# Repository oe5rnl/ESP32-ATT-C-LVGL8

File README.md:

# Attenuator Controller

Das Projekt realisiert einen Controller für RF-Attenuators (HF-Dämpfungsglieder).

Es besteht aus einer Basisplatine und den optionalen Bendienelementen:  
* Ein ESP32 CYD Touch-Display  
* Ein 2.8" OLED Display  
* Einen Drehgeber mit Druckschalter  

Der Betrieb kann in folgenden Varianten erfolgen. Basisplatine **und**:  
* Nur ESP Touch Display
* OLED Display und Drehgeber
* ESP Touch Display und oder/und OLED sowie oder/und Drehgeber 

### Firmware installieren (ohne Installation)

Für Endnutzer gibt es im Ordner [install/](install/) einen Offline-Flasher, der
ohne PlatformIO oder Python auskommt — es wird nur ein mitgeliefertes Programm
aufgerufen. Details siehe [install/README.md](install/README.md).

- **ESP32:** Board per USB anstecken und `flash-esp32.sh` (Linux) bzw.
  `flash-esp32.bat` (Windows) ausführen. Der serielle Port wird automatisch
  erkannt; das eigenständige `esptool` ist bereits enthalten.
- **Pico:** **BOOTSEL** gedrückt halten, einstecken und `firmware/firmware.uf2`
  auf das Laufwerk `RPI-RP2` kopieren — ganz ohne Zusatzprogramm.

> **Hinweis:** Die auslieferbaren Firmware-Dateien werden vom Entwickler einmalig
> per [install/export.sh](install/export.sh) erzeugt (baut ESP32 + Pico und legt
> `firmware-merged.bin` sowie `firmware.uf2` in `install/firmware/` ab).

---

## Systemübersicht

ESP32 CYD (Touch-Display 320×240, WebGUI via WiFi, LVGL 8 UI) kommuniziert über
UART (115200 Baud) mit dem Raspberry Pi Pico (Drehgeber, SSD1306 OLED). Beide
steuern gemeinsam die Attenuator-Relais.

Der am häufigsten Abzutreffende Attenuatos ist die 135dB Variante.  
Siehe dazu zur Verkabelung ATT_135db.md  
Test der EinzelRelais mit dem Testmenü am Display und auf der Webseite.

### ESP32 — Touch-Controller

LVGL-8-Steuerungsoberfläche auf ESP32 CYD (Cheap Yellow Display):

- 2.8" Touch-Display ILI9341 (320×240), Variante CYD2USB mit ST7789
- WLAN: AP-Modus und Client-Modus gleichzeitig
- WebGUI mit identischer Funktion wie das Touch-Display
- NVS-Persistenz (Wert, Presets, WiFi-Modus, Set-Modus)
- FreeRTOS Dual-Core: LVGL/UI auf Core 1, WebSocket/WiFi auf Core 0
- Kommunikation mit dem Pico über UART0

### Pico — Relais-/Drehgeber-Controller

Raspberry Pi Pico als Attenuator-Controller:

- Drehgeber zur Auswahl und Aktivierung von Dämpfungswerten
- Optionales SSD1306 OLED-Display (I2C)
- Automatische Attenuator-Erkennung über ADC (Spannungsteiler an GP26 / ADC0)
- Bis zu 8 bistabile Relais (H-Brücke oder Einzel-Pin)
- Serielle Steuerung über UART vom ESP32

---

## Unterstützte Attenuatoren

Quelle: [pico/src/Attenuator.cpp](pico/src/Attenuator.cpp),
[pico/src/att_types.h](pico/src/att_types.h) und die jeweiligen `att_*`-Klassen.

| Typ | Max. dB | Schritte | Relay-Modus | Status im Code |
|-----|--------:|---------:|-------------|----------------|
| R&S 26.5 GHz | 110 dB | 10 dB | Static (Einzelpin) | implementiert (`Att26GHz`) |
| R&S RS-135 dB | 135 dB | 5 dB | Bridge (H-Brücke) | implementiert (`Att135dB`) |
| RS-141 dB | (variable Pads) | — | Bridge (H-Brücke) | implementiert (`Att141dB`) |
| Typ B | — | — | — | **nicht** implementiert (`AttB` → „NOT IMPLEMENTED") |

### Automatische Erkennung über ADC (GP26 / ADC0)

**Maßgeblich ist der Code** in [pico/src/main.cpp](pico/src/main.cpp) (`getAttenuator()`):

| Spannung (v) | Erkannter Attenuator |
|--------------|----------------------|
| 0.0 V ≤ v < 0.7 V | RS-141 dB |
| 0.9 V ≤ v < 1.5 V | 26.5 GHz |
| 1.7 V ≤ v < 2.3 V | Typ B |
| 2.4 V ≤ v ≤ 3.3 V | RS-135 dB |
| außerhalb aller Fenster | **NOT IMPLEMENTED** — kein Attenuator, kein GPIO wird gesetzt |

> **Hinweis:** Die alten READMEs und der Kommentar in
> [pico/src/att_types.h](pico/src/att_types.h) nennen eine andere Zuordnung
> (0.0–0.8 V → 26.5 GHz usw.). Diese stimmt **nicht** mit dem aktuellen Code
> überein. Ungültige Spannungen (Lücken 0.7–0.9 / 1.5–1.7 / 2.3–2.4 V sowie alles
> außerhalb) liefern `getAttenuator()` = `-1`; `create_attenuator()` gibt dann
> `nullptr` zurück, es wird **kein GPIO** aktiviert und das Display zeigt
> „NOT IMPLEMENTED".

### Widerstände für den Spannungsteiler

R10 nach 3,3 V, R11 nach GND (an Pico ADC):

```
 3,3V
  |
 R10
  |---- Pico ADC (GP26)
  |
 R11
  |
 GND
```

| Attenuator | R10 | R11 |
|------------|-----|-----|
| 26.5 GHz | offen | offen |
| RS-141 dB | 3k3 | 4k7 |
| Typ B | 4k7 | 3k3 |
| RS-135 dB | 0 Ohm | offen |

> **ACHTUNG:** Niemals zwei 0-Ohm-Widerstände einbauen — das kurzschließt den
> 3,3-V-Ausgang des Pico.
>
> **ACHTUNG:** Vor dem Verbinden des Attenuators mit der Steuerplatine am Display
> prüfen, ob der gewünschte Attenuator angezeigt wird. Wird `ATTENUATOR_26_5GHz`
> eingestellt, aber ein Attenuator mit H-Brücken-Ansteuerung verwendet, kann es
> zur Zerstörung der Relais führen.

---

## Hardware

### Pico — GPIO-Belegung

| Pin | GPIO | Funktion |
|-----|------|----------|
| 1  | GP0  | TX → ESP32 (Serial1) |
| 2  | GP1  | RX ← ESP32 (Serial1) |
| 4  | GP2  | Relais 1a |
| 5  | GP3  | Relais 1b |
| 6  | GP4  | I2C SDA (Display) |
| 7  | GP5  | I2C SCL (Display) |
| 9  | GP6  | Relais 2a |
| 10 | GP7  | Relais 2b |
| 11 | GP8  | Relais 3a |
| 12 | GP9  | Relais 3b |
| 14 | GP10 | Relais 4a |
| 15 | GP11 | Relais 4b |
| 16 | GP12 | Relais 5a |
| 17 | GP13 | Relais 5b |
| 19 | GP14 | Relais 6a |
| 20 | GP15 | Relais 6b |
| 21 | GP16 | Relais 7a |
| 22 | GP17 | Relais 7a |
| 24 | GP18 | Relais 8a |
| 25 | GP19 | Encoder SW |
| 26 | GP20 | Encoder DT (B) |   
| 27 | GP21 | Encoder CLK (A) |
| 29 | GP22 | Relais 8b |
| 31 | GP26 | ADC0 — Attenuator-Erkennung |
| 32 | GP27 | Relais 9a |
| 34 | GP28 | Relais 9b |

#### Relais-Mapping RS-135 dB (bistabil, ON/OFF-Pin-Paare)

Quelle: [pico/src/att_135db.h](pico/src/att_135db.h) / [.cpp](pico/src/att_135db.cpp).

| Relais | ON-Pin | OFF-Pin | tatsächlicher Pad-Wert |
|--------|--------|---------|------------------------|
| U1 (40bB A) | GP3 | GP2 | 40 dB |
| U2 (20dB A) | GP7 | GP6 | 20 dB |
| U3 (5 dB) | GP9 | GP8 | 5 dB |
| U4 (20dB B) | GP11 | GP10 | 20 dB |
| U5 (10 dB) | GP13 | GP12 | 10 dB |
| U6 (40dB B) | GP15 | GP14 | 40 dB |
| U7 (RF) | GP17 | GP16 | RF ON/OFF |

#### Relais-Mapping 26.5 GHz (Static, HIGH = aktiv)

Quelle: [pico/src/att_26ghz.h](pico/src/att_26ghz.h).

| Pad | GPIO | Pin |
|-----|------|-----|
| 10 dB | GP10 | 14 |
| 20 dB | GP11 | 15 |
| 40 dB (A) | GP12 | 16 |
| 40 dB (B) | GP13 | 17 |

---

## WiFi-Konfiguration

### WiFi-Credentials einstellen

Erstelle `esp32/src/wifi_credentials.h` mit deinen WLAN-Zugangsdaten (Vorlage:
[esp32/src/wifi_credentials.h.example](esp32/src/wifi_credentials.h.example)):

Der AP ist unabhängig von der Datei stets erreichbar. Die Client-Anbindung ans Heimnetz kann man jederzeit zur Laufzeit über die WebGUII (WLAN-Suche → Verbinden) oder das Display setzen — die Werte landen im NVS. wifi_credentials.h ist nur praktisch, wenn man die Zugangsdaten schon beim Kompilieren fest hinterlegen will (z. B. damit sich das Gerät ohne manuelle Ersteinrichtung direkt verbindet).

```cpp
#pragma once
#define WIFI_SSID     "DeinSSID"
#define WIFI_PASSWORD "DeinPasswort"
```

Diese Datei ist in [.gitignore](.gitignore) und wird nicht committet.

### WiFi-Modi

Quelle: [esp32/src/webserver.h](esp32/src/webserver.h) (`apply_wifi_mode()`).

Es gibt genau **zwei** Modi; jeder von 0 verschiedene Wert wird intern auf `2`
gesetzt. Die Einstellung wird im NVS (`wmode`) gespeichert.

- **Modus 0 (Aus):** WiFi vollständig deaktiviert (`WIFI_OFF`), Webserver und AP
  werden gestoppt, mDNS beendet.
- **Modus 2 (AP + Client):** Der Access Point ist **immer** aktiv. Ein
  Client (STA) wird zusätzlich nur gestartet, wenn gültige Client-Zugangsdaten
  vorliegen — andernfalls läuft das Gerät im AP-only-Betrieb.
  - AP-SSID: `ESP32-ATT`
  - AP-Passwort: `12345678` (Standardwert — bitte ändern)
  - AP-IP: `192.168.4.1`
  - Client-Zugangsdaten stammen aus dem NVS (`wifi_ssid` / `wifi_pass`),
    vorbelegt aus [esp32/src/wifi_credentials.h](esp32/src/wifi_credentials.h);
    zur Laufzeit über das Display-Menü (**Menu → WLAN**) bzw. die WLAN-Suche der
    WebGUI setzbar.
  - Die Client-Verbindung erfolgt nicht blockierend; nach Timeout (ca. 20 s) oder
    bei Fehler fällt das Gerät automatisch auf AP-only zurück.
  - mDNS (`esp32-att.local`) wird erst nach erfolgreicher Client-Verbindung
    aktiviert.

### WebGUI

Nach dem Start erreichbar unter:
- **AP-Modus:** `http://192.168.4.1`
- **Client-Modus:** `http://esp32-att.local` (oder die angezeigte IP)

---

## Quick Start

### ESP32 flashen
```bash
cd esp32
./upload.sh
# oder manuell:
~/.platformio/penv/bin/pio run -t upload
~/.platformio/penv/bin/pio device monitor
# CYD2USB-Variante (ST7789):
~/.platformio/penv/bin/pio run -e cyd2usb -t upload
```

### Pico flashen
```bash
cd pico
./upload_main.sh
# oder manuell:
~/.platformio/penv/bin/pio run -t upload
~/.platformio/penv/bin/pio device monitor
```

> **Tipp:** Falls `pio: command not found` erscheint, den vollen Pfad
> `~/.platformio/penv/bin/pio` verwenden oder PlatformIO global installieren.

**Voraussetzungen:** [PlatformIO](https://platformio.org/) (CLI oder VS-Code-Extension).

### Tools einrichten

1. **Repository holen**
   ```bash
   git clone <REPO-URL>
   cd ESP32-ATT-C-LVGL8
   ```

2. **PlatformIO installieren** — eine der beiden Varianten:
   - **VS Code + Extension (empfohlen):** [VS Code](https://code.visualstudio.com/)
     installieren, dann die Extension **PlatformIO IDE** hinzufügen. Build/Upload
     erfolgen über die PlatformIO-Toolbar.
   - **CLI (Kommandozeile):**
     ```bash
     python3 -m pip install --user platformio
     # oder das offizielle Installskript:
     # curl -fsSL https://raw.githubusercontent.com/platformio/platformio-core-installer/master/get-platformio.py | python3
     ```
     Danach steht `pio` unter `~/.platformio/penv/bin/pio` zur Verfügung
     (ggf. in den `PATH` aufnehmen).

3. **Toolchains & Bibliotheken** — werden beim ersten `pio run` automatisch
   geladen (Platforms `espressif32` und `raspberrypi`, Frameworks und alle
   `lib_deps` aus den jeweiligen [platformio.ini](esp32/platformio.ini)).
   Eine manuelle Installation ist nicht nötig.

4. **Serielle Rechte (Linux):** Für Upload/Monitor den eigenen Benutzer zur
   Gruppe `dialout` hinzufügen und neu anmelden:
   ```bash
   sudo usermod -aG dialout $USER
   ```

5. **WLAN-Zugangsdaten (optional):** Nur nötig, wenn die Client-Zugangsdaten
   bereits beim Kompilieren fest hinterlegt werden sollen — siehe Abschnitt
   „WiFi-Credentials einstellen". Ohne diese Datei ist der Access Point trotzdem
   erreichbar; die Client-Anbindung lässt sich zur Laufzeit über WebGUI/Display
   setzen.

---

## Serielles Kommunikationsprotokoll (UART, 115200 Baud)

Alle Nachrichten sind ASCII-Zeilen, abgeschlossen mit `\n`.

### Pico → ESP32

**Startup-Info** (einmalig nach Pico-Reset):

| Befehl | Beschreibung |
|--------|--------------|
| `RELAYS:<n>` | Anzahl der Relais |
| `ATTNAME:<name>` | Attenuator-Name |
| `STEP:<n>` | Schrittweite in dB |
| `MAXDB:<n>` | Maximalwert in dB |
| `RELMODE:<n>` | Relay-Modus: `0`=Bridge, `1`=Static |
| `RFSWITCH:<n>` | RF-Schalter vorhanden: `0`/`1` |
| `PICOVER:<ver>` | Pico-Firmware-Version |

**Laufzeit:**

| Befehl | Beschreibung |
|--------|--------------|
| `<n>dB` | Aktueller Dämpfungswert (Display-Sync) |
| `SEL<n>` | Ausgewählte Stelle: `0`=Hunderter, `1`=Zehner, `2`=Einer |
| `SETMODE:<n>` | Set-Modus: `0`=Direct, `1`=Time, `2`=Button |
| `RF:<n>` | RF-Schalter-Zustand: `0`/`1` |
| `TESTSTATE:<i>,<s>` | Test: Relais-Index `i`, Zustand `s` (`0`/`1`) |
| `SETOK` | Pico hat im Set-Button-Modus angewendet |

### ESP32 → Pico

| Befehl | Beschreibung |
|--------|--------------|
| `<n>dB` | Dämpfung Display-Sync (kein Schalten) |
| `SET:<n>dB` | Dämpfung sofort schalten (Relais) |
| `TIMED:<n>dB` | Zeitgesteuert schalten |
| `SEL<n>` | Aktive Stelle ändern |
| `SETMODE:<n>` | Set-Modus umschalten |
| `RF:<n>` | RF-Schalter setzen: `0`/`1` |
| `TEST:START` | Relay-Test starten |
| `TEST:SEL:<i>` | Test-Relais `i` auswählen |
| `TEST:ACTION` | Test: Puls/Toggle am gewählten Relais |
| `TEST:END` | Test beenden |

---

## Implementierungsdetails ESP32

| Core | Aufgaben |
|------|----------|
| **Core 0** | WiFi-Stack, AsyncTCP, ESPAsyncWebServer, WebSocket-Callbacks |
| **Core 1** | `setup()` / `loop()`, LVGL `lv_timer_handler()`, UART-Empfang |

Kommunikation zwischen den Cores über FreeRTOS-Queue (`xQueueSend` / `xQueueReceive`).

---

## Projektstruktur

```
ESP32-ATT-C-LVGL8/
├── shared/
│   └── version.h               # Versionsnummern ESP32 + Pico (0.51)
├── esp32/
│   ├── platformio.ini          # PlatformIO + TFT_eSPI Build-Flags
│   ├── lv_conf.h               # LVGL-8-Konfiguration
│   └── src/
│       ├── main.cpp            # LVGL UI, UART-Kommunikation
│       ├── webserver.h         # AsyncWebServer, WebSocket, HTML
│       ├── wifi_credentials.h  # WLAN-Zugangsdaten (nicht im Repo)
│       └── lv_font_digits_72.c # Custom 72 px Ziffern-Font
├── pico/
│   └── src/
│       ├── main.cpp            # Hauptprogramm, UART, Encoder, ADC-Erkennung
│       ├── Attenuator.h/.cpp   # Abstrakte Basisklasse + Factory
│       ├── att_26ghz.h/.cpp    # R&S 26.5 GHz (Static, 110 dB / 10 dB)
│       ├── att_135db.h/.cpp    # R&S 135 dB (Bridge, 135 dB / 5 dB)
│       ├── att_141db.h/.cpp    # RS-141 dB (Bridge)
│       ├── att_b.h/.cpp        # Typ B (nicht implementiert)
│       ├── att_types.h         # Typ-Konstanten + ADC-Grenzwerte (Kommentar veraltet)
│       ├── test.h/.cpp         # Relay-Testmodus
│       ├── SSD1306.h/.cpp      # OLED-Display-Treiber
│       ├── big_digits.h        # Große Ziffern für OLED
│       ├── font.h              # OLED-Font
│       └── toggle_gpio10_13.cpp # Standalone-GPIO-Testhilfe
├── Schaltung/                  # KiCad Schaltplan + PCB
├── install/                    # Offline-Flasher (esptool + Skripte, ohne Installation)
└── docs/                       # Zusätzliche Dokumentation
```

---

## Lizenz

MIT — siehe [LICENSE](LICENSE).

Ausnahme: Der Ordner [esp32/docu/esp32-display/](esp32/docu/esp32-display/)
enthält Hersteller-Dokumentation (Sunton) und ist **nicht** von der MIT-Lizenz
abgedeckt.

Build by OE5RNL & OE5NVL & Chatgpt & Claude

### Haftungsausschluss

Diese Hard- und Software wird „wie besehen" ohne jegliche Gewährleistung
bereitgestellt — weder ausdrücklich noch stillschweigend, insbesondere keine
Gewährleistung der Marktgängigkeit oder Eignung für einen bestimmten Zweck.
Die Nutzung erfolgt auf eigene Gefahr. Die Autoren übernehmen keine Haftung für
Schäden jeglicher Art (z. B. an Attenuatoren, Relais, Messgeräten oder sonstiger
Ausrüstung), die aus dem Aufbau, dem Betrieb oder der Nutzung dieses Projekts
entstehen.

Insbesondere kann eine falsche Attenuator-Erkennung oder fehlerhafte Verdrahtung
zur Zerstörung der Relais oder des angeschlossenen Dämpfungsglieds führen (siehe
Warnhinweise im Abschnitt „Widerstände für den Spannungsteiler"). Vor dem
Anschluss stets prüfen, ob der korrekte Attenuator angezeigt wird.

## Basiert auf

[ESP32-Cheap-Yellow-Display](https://github.com/witnessmenow/ESP32-Cheap-Yellow-Display)
— LVGL8-Beispiel.

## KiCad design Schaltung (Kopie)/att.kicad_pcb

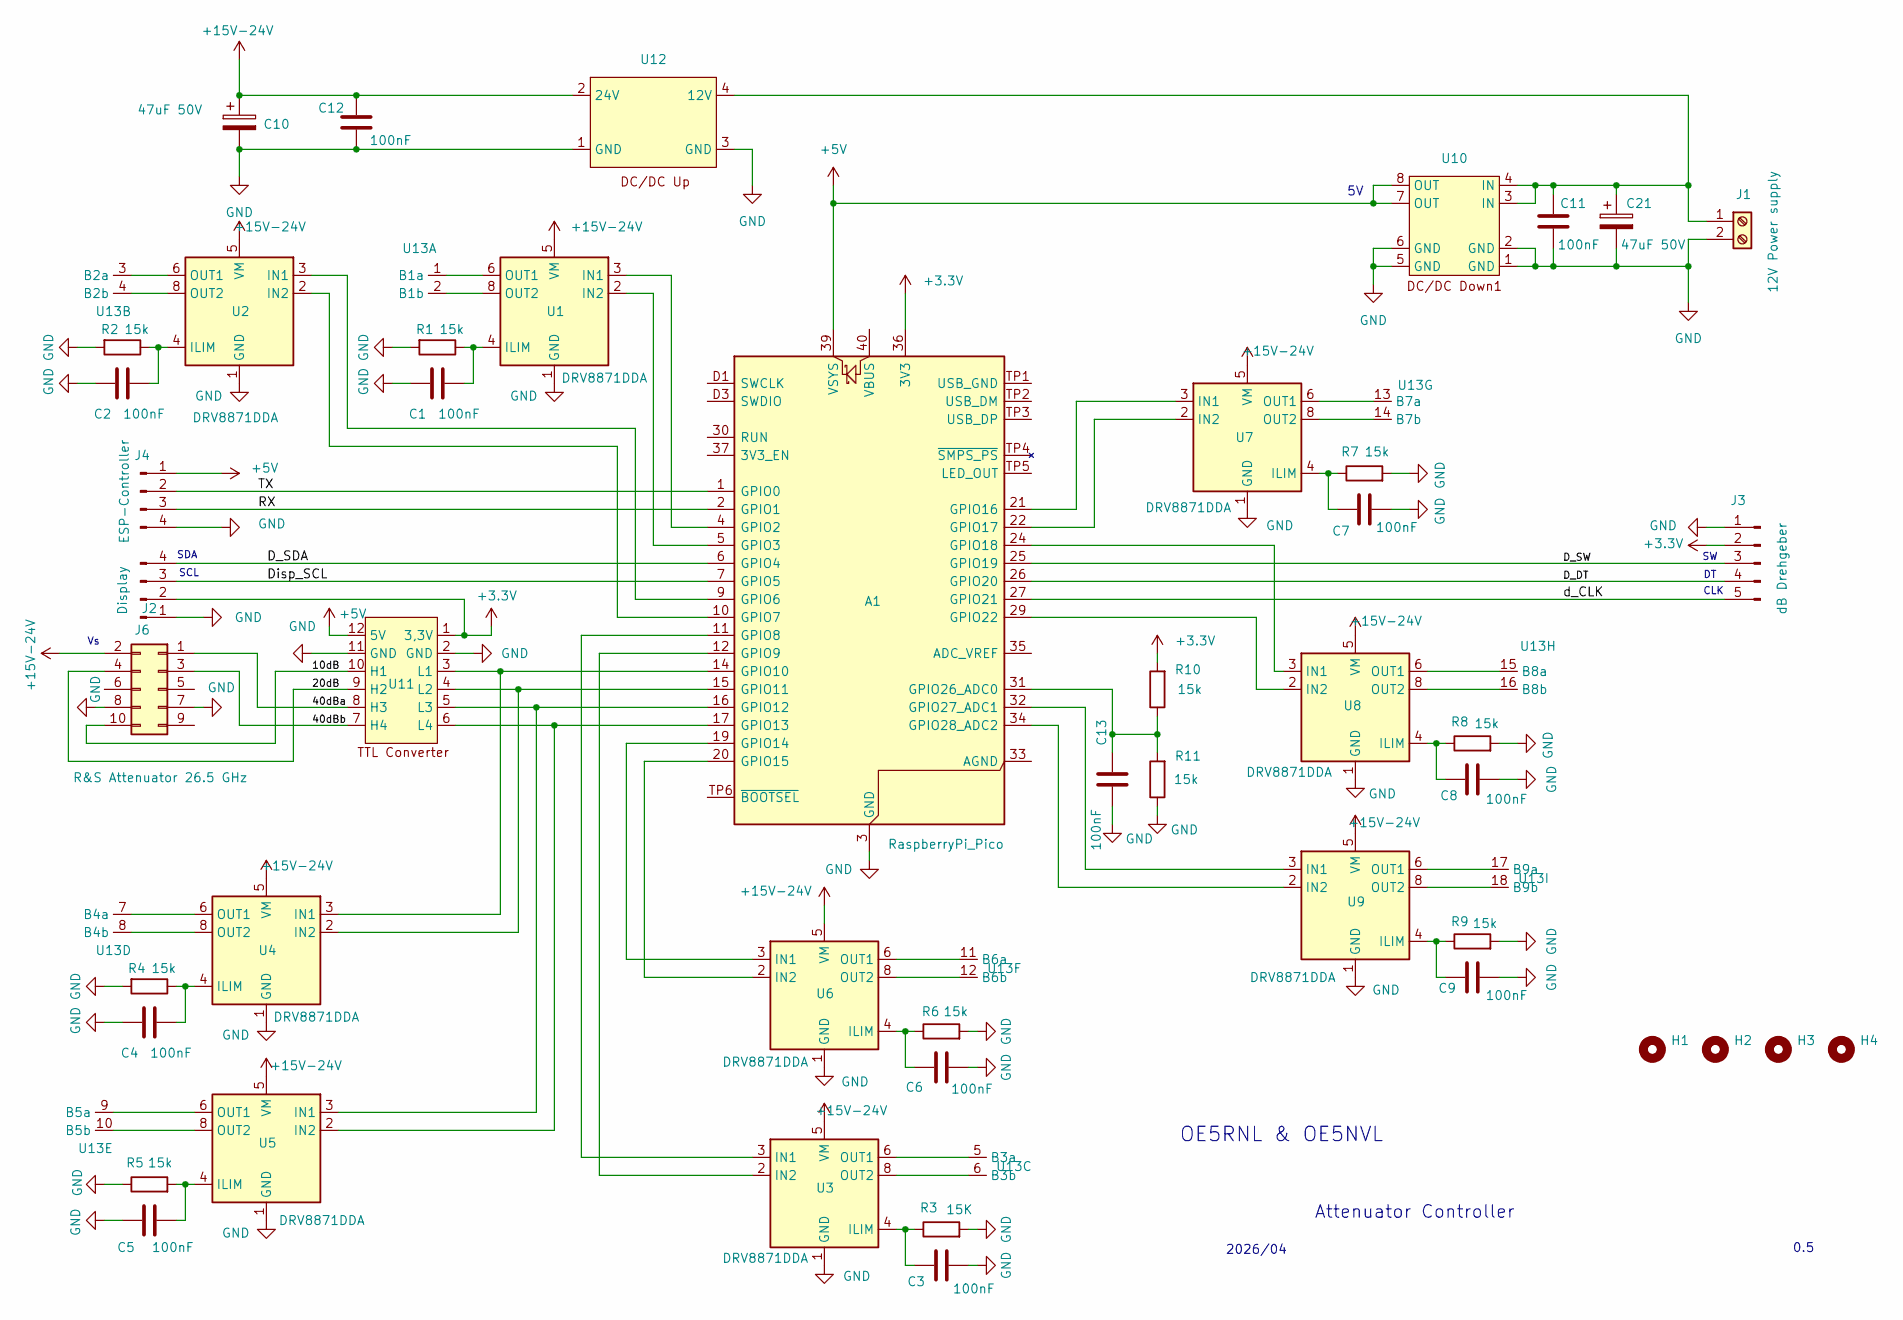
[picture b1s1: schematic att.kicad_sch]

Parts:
A1: RaspberryPi_Pico; RaspberryPi_Pico_SMD
C1, C2, C3, C4, C5, C6, C7, C8, C9, C11, C12, C13: 100nF; C_0805_2012Metric
C10: 47uF 50V; CP_Radial_D8.0mm_P5.00mm
C21: 47uF 50V; CP_Elec_6.3x5.2
H1, H2, H3, H4: MountingHole; MountingHole_2.5mm
J1: 12V Power supply; TerminalBlock_MetzConnect_Type055_RT01502HDWU_1x02_P5.00mm_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
J2: R&S Attenuator 26.5 GHz; PinHeader_2x05_P2.54mm_Vertical
J3: dB Drehgeber; PinHeader_1x05_P2.54mm_Vertical
J4: ESP-Controller; PinHeader_1x04_P2.54mm_Vertical
J6: Display; PinHeader_1x04_P2.54mm_Vertical
R1, R2, R4, R5, R6, R7, R8, R9, R10, R11: 15k; R_0805_2012Metric
R3: 15K; R_0805_2012Metric
U1, U2, U3, U4, U5, U6, U7, U8, U9: DRV8871DDA; Texas_HTSOP-8-1EP_3.9x4.9mm_P1.27mm_EP2.95x4.9mm_Mask2.4x3.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
U10: DC-DC_12_5
U11: ttl_converter
U12: DC-DC_12_24
U13: SIL_18

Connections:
+3.3V: A1.36 (3V3), J3.2, J6.2, R10.2, U11.1 (3,3V)
+5V: A1.39 (VSYS), J4.1, U10.7 (OUT), U10.8 (OUT), U11.12 (5V)
+15V-24V: C10.1, C12.2, J2.2 (Pin_10), U1.5 (VM), U2.5 (VM), U3.5 (VM), U4.5 (VM), U5.5 (VM), U6.5 (VM), U7.5 (VM), U8.5 (VM), U9.5 (VM), U12.2 (24V)
/10dB: J2.10 (Pin_6), U11.10 (H1)
/20dB: J2.4 (Pin_9), U11.9 (H2)
/40dBa: J2.1, U11.8 (H3)
/40dBb: J2.3 (Pin_2), U11.7 (H4)
/D_DT: A1.26 (GPIO20), J3.4
/D_SDA: A1.6 (GPIO4), J6.4
/D_SW: A1.25 (GPIO19), J3.3
/Disp_SCL: A1.7 (GPIO5), J6.3
/RX: A1.2 (GPIO1), J4.3
/TX: A1.1 (GPIO0), J4.2
/d_CLK: A1.27 (GPIO21), J3.5
GND: A1.3 (GND), A1.8 (GND), A1.13 (GND), A1.18 (GND), A1.23 (GND), A1.28 (GND), A1.38 (GND), A1.D2 (GND), C1.1, C2.1, C3.2, C4.1, C5.1, C6.2, C7.2, C8.2, C9.2, C10.2, C11.1, C12.1, C13.1, C21.2, J1.2, J2.7 (Pin_4), J2.8 (Pin_7), J3.1, J4.4, J6.1, R1.2, R2.2, R3.2, R4.2, R5.1, R6.2, R7.2, R8.2, R9.2, R11.1, U1.1 (GND), U1.7 (GND), U1.9 (GND), U2.1 (GND), U2.7 (GND), U2.9 (GND), U3.1 (GND), U3.7 (GND), U3.9 (GND), U4.1 (GND), U4.7 (GND), U4.9 (GND), U5.1 (GND), U5.7 (GND), U5.9 (GND), U6.1 (GND), U6.7 (GND), U6.9 (GND), U7.1 (GND), U7.7 (GND), U7.9 (GND), U8.1 (GND), U8.7 (GND), U8.9 (GND), U9.1 (GND), U9.7 (GND), U9.9 (GND), U10.1 (GND), U10.2 (GND), U10.5 (GND), U10.6 (GND), U11.2 (GND), U11.11 (GND), U12.1 (GND), U12.3 (GND)
unnamed: A1.4 (GPIO2), U1.3 (IN1)
unnamed: A1.5 (GPIO3), U1.2 (IN2)
unnamed: A1.9 (GPIO6), U2.3 (IN1)
unnamed: A1.10 (GPIO7), U2.2 (IN2)
unnamed: A1.11 (GPIO8), U3.3 (IN1)
unnamed: A1.12 (GPIO9), U3.2 (IN2)
unnamed: A1.14 (GPIO10), U4.3 (IN1), U11.3 (L1)
unnamed: A1.15 (GPIO11), U4.2 (IN2), U11.4 (L2)
unnamed: A1.16 (GPIO12), U5.3 (IN1), U11.5 (L3)
unnamed: A1.17 (GPIO13), U5.2 (IN2), U11.6 (L4)
unnamed: A1.19 (GPIO14), U6.3 (IN1)
unnamed: A1.20 (GPIO15), U6.2 (IN2)
unnamed: A1.21 (GPIO16), U7.3 (IN1)
unnamed: A1.22 (GPIO17), U7.2 (IN2)
unnamed: A1.24 (GPIO18), U8.3 (IN1)
unnamed: A1.29 (GPIO22), U8.2 (IN2)
unnamed: A1.31 (GPIO26_ADC0), C13.2, R10.1, R11.2
unnamed: A1.32 (GPIO27_ADC1), U9.3 (IN1)
unnamed: A1.34 (GPIO28_ADC2), U9.2 (IN2)
unnamed: C11.2, C21.1, J1.1, U10.3 (IN), U10.4 (IN), U12.4 (12V)
unnamed: C1.2, R1.1, U1.4 (ILIM)
unnamed: U1.6 (OUT1), U13.1 (B1a)
unnamed: U1.8 (OUT2), U13.2 (B1b)
unnamed: C2.2, R2.1, U2.4 (ILIM)
unnamed: C3.1, R3.1, U3.4 (ILIM)
unnamed: C4.2, R4.1, U4.4 (ILIM)
unnamed: C5.2, R5.2, U5.4 (ILIM)
unnamed: C6.1, R6.1, U6.4 (ILIM)
unnamed: C7.1, R7.1, U7.4 (ILIM)
unnamed: C8.1, R8.1, U8.4 (ILIM)
unnamed: C9.1, R9.1, U9.4 (ILIM)
unnamed: U2.6 (OUT1), U13.3 (B2a)
unnamed: U2.8 (OUT2), U13.4 (B2b)
unnamed: U3.6 (OUT1), U13.5 (B3a)
unnamed: U3.8 (OUT2), U13.6 (B3b)
unnamed: U4.6 (OUT1), U13.7 (B4a)
unnamed: U4.8 (OUT2), U13.8 (B4b)
unnamed: U5.6 (OUT1), U13.9 (B5a)
unnamed: U5.8 (OUT2), U13.10 (B5b)
unnamed: U6.6 (OUT1), U13.11 (B6a)
unnamed: U6.8 (OUT2), U13.12 (B6b)
unnamed: U7.6 (OUT1), U13.13 (B7a)
unnamed: U7.8 (OUT2), U13.14 (B7b)
unnamed: U8.6 (OUT1), U13.15 (B8a)
unnamed: U8.8 (OUT2), U13.16 (B8b)
unnamed: U9.6 (OUT1), U13.17 (B9a)
unnamed: U9.8 (OUT2), U13.18 (B9b)

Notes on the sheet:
Attenuator Controller
0.5
OE5RNL & OE5NVL
CLK
SCL
SDA
2026/04

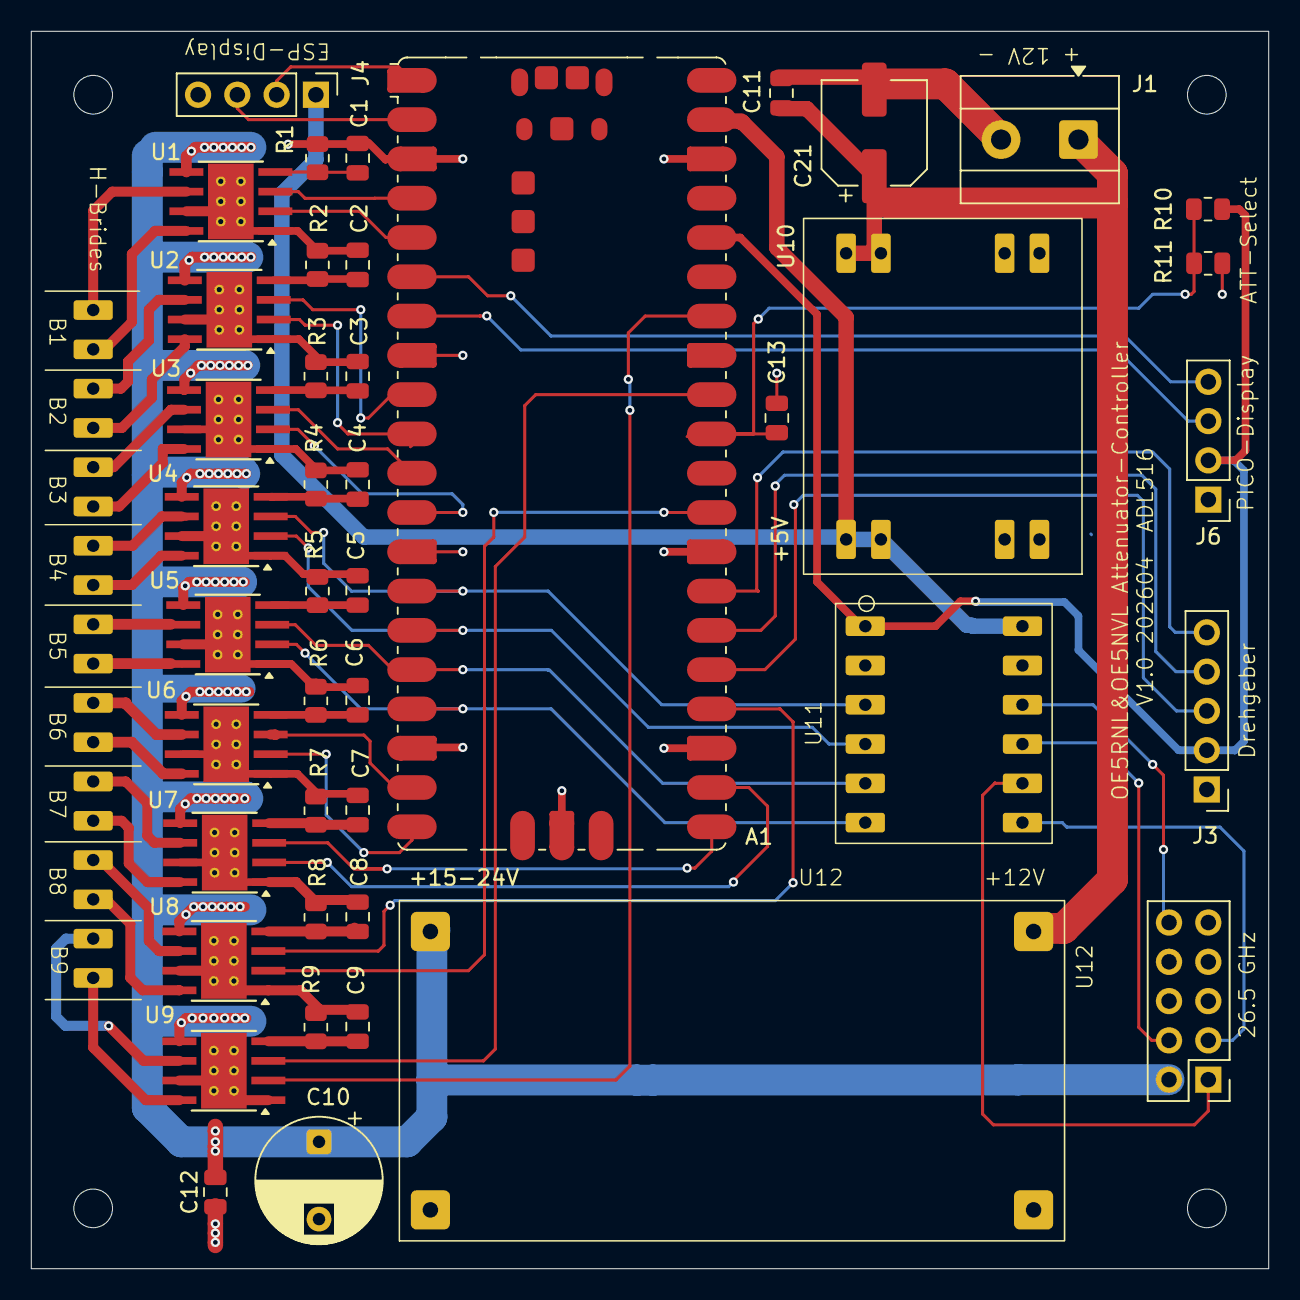
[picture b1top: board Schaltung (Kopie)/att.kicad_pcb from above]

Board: 2 copper layers, 80.0 x 80.0 mm, 48 parts (0 on the bottom side), 62 nets.

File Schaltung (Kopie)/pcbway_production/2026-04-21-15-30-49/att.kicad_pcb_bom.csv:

Designator,Quantity,Value,Footprint,Package,MPN,DNP,Mount_Type,Description,KiLib_Generator
A1,1,RaspberryPi_Pico,RaspberryPi_Pico_SMD,,,,smt,"Versatile and inexpensive microcontroller module (with full pinout for test point and debug connections) powered by RP2040 dual-core Arm Cortex-M0+ processor up to 133 MHz, 264kB SRAM, 2MB QSPI flash; also supports Raspberry Pi Pico 2",
"C1, C11, C12, C13, C2, C3, C4, C5, C6, C7, C8, C9",12,100nF,C_0805_2012Metric,,,,smt,Unpolarized capacitor,SMD_2terminal_chip_molded
C10,1,47uF 50V,CP_Radial_D8.0mm_P5.00mm,,,,tht,Polarized capacitor,capacitor/THT/other
C21,1,47uF 50V,CP_Elec_6.3x5.2,,,,smt,Polarized capacitor,capacitor/SMD/elec_round_polarized
J1,1,12V Power supply,TerminalBlock_MetzConnect_Type055_RT01502HDWU_1x02_P5.00mm_Horizontal,,,,tht,"Generic screw terminal, single row, 01x02, script generated (kicad-library-utils/schlib/autogen/connector/)",terminal_block/Metz_Connect
J2,1,R&S Attenuator 26.5 GHz,PinHeader_2x05_P2.54mm_Vertical,,,,tht,"Generic connector, double row, 02x05, counter clockwise pin numbering scheme (similar to DIP package numbering), script generated (kicad-library-utils/schlib/autogen/connector/)",connector/pin_header_socket
J3,1,dB Drehgeber,PinHeader_1x05_P2.54mm_Vertical,,,,tht,"Generic connector, single row, 01x05, script generated",connector/pin_header_socket
J4,1,ESP-Controller,PinHeader_1x04_P2.54mm_Vertical,,,,tht,"Generic connector, single row, 01x04, script generated",connector/pin_header_socket
J6,1,Display,PinHeader_1x04_P2.54mm_Vertical,,,,tht,"Generic connector, single row, 01x04, script generated",connector/pin_header_socket
"R1, R10, R11, R2, R4, R5, R6, R7, R8, R9",10,15k,R_0805_2012Metric,,,,smt,Resistor,SMD_2terminal_chip_molded
R3,1,15K,R_0805_2012Metric,,,,smt,Resistor,SMD_2terminal_chip_molded
"U1, U2, U3, U4, U5, U6, U7, U8, U9",9,DRV8871DDA,Texas_HTSOP-8-1EP_3.9x4.9mm_P1.27mm_EP2.95x4.9mm_Mask2.4x3.1mm_ThermalVias,,,,smt,"Brushed DC Motor Driver, PWM Control, 45V, 3.6A, Current limiting, HTSOP-8",
U10,1,~,DC-DC_12_5,,,,smt,,
U11,1,~,ttl_converter,,,,smt,,
U12,1,~,DC-DC_12_24,,,,smt,,
U13,1,~,SIL_18,,,,smt,,

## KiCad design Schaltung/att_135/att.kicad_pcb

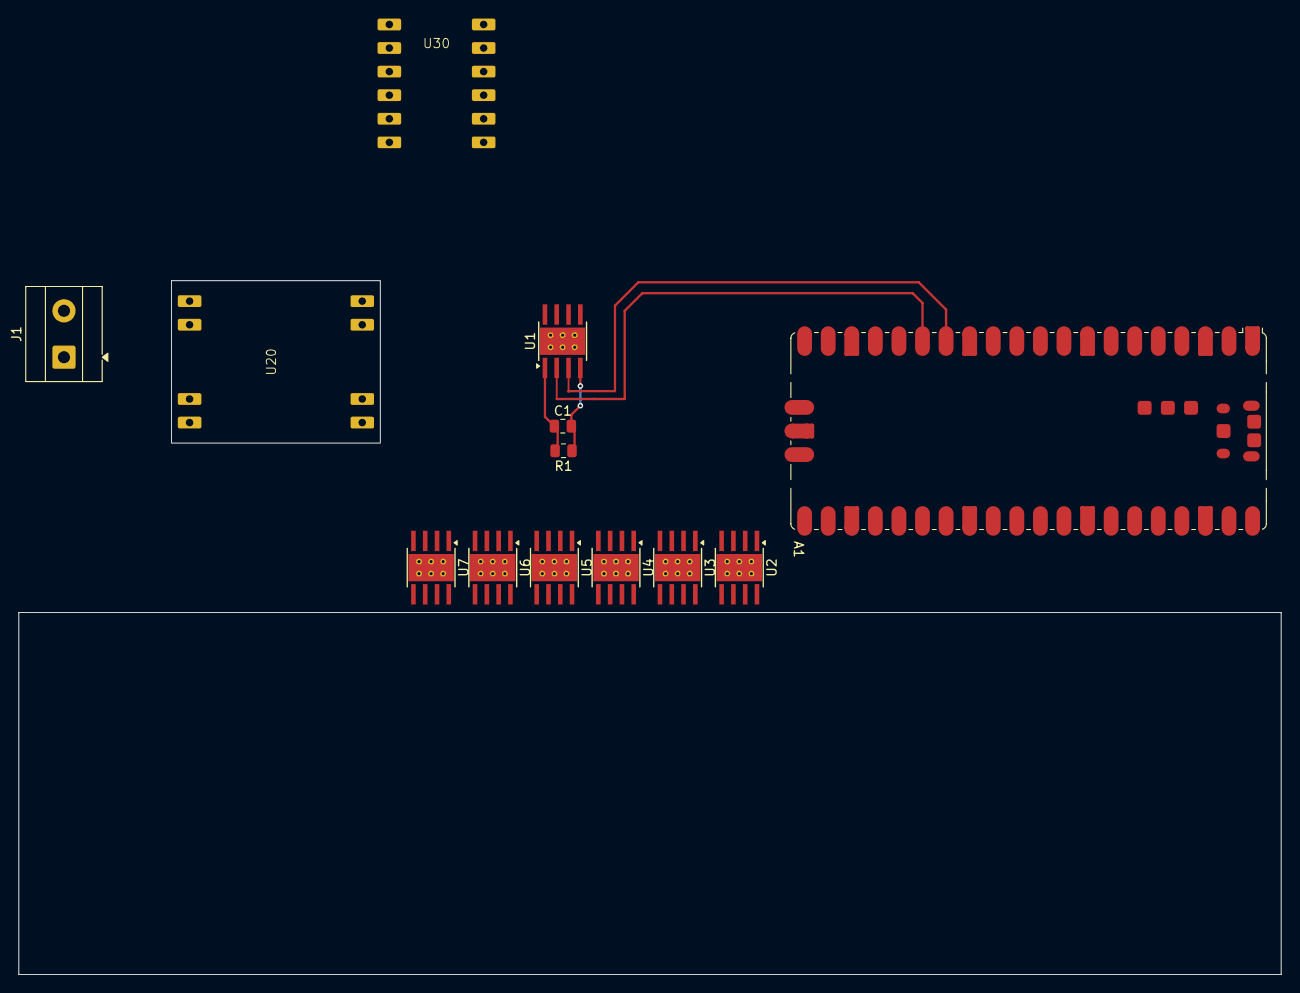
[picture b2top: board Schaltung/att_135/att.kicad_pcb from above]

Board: 2 copper layers, 136.0 x 74.8 mm, 13 parts (0 on the bottom side), 19 nets.

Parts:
A1: RaspberryPi_Pico; RaspberryPi_Pico_SMD
C1: 100nF; R_0805_2012Metric
J1: 12V Power supply; TerminalBlock_MetzConnect_Type055_RT01502HDWU_1x02_P5.00mm_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
R1: 15k; R_0805_2012Metric
U1, U2, U3, U4, U5, U6, U7: DRV8871DDA; Texas_HTSOP-8-1EP_3.9x4.9mm_P1.27mm_EP2.95x4.9mm_Mask2.4x3.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
U20: MP1584EN_module
U30: ttl_converter

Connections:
+5V: A1.39 (VSYS), U20.7 (OUT), U20.8 (OUT)
+15V: U1.5 (VM), U2.5 (VM), U3.5 (VM), U4.5 (VM), U5.5 (VM), U6.5 (VM), U7.5 (VM)
GND: A1.3 (GND), A1.8 (GND), A1.13 (GND), A1.18 (GND), A1.23 (GND), A1.28 (GND), A1.38 (GND), A1.D2 (GND), C1.1, J1.2, R1.2, U1.1 (GND), U1.7 (GND), U1.9 (GND), U2.1 (GND), U2.7 (GND), U2.9 (GND), U3.1 (GND), U3.7 (GND), U3.9 (GND), U4.1 (GND), U4.7 (GND), U4.9 (GND), U5.1 (GND), U5.7 (GND), U5.9 (GND), U6.1 (GND), U6.7 (GND), U6.9 (GND), U7.1 (GND), U7.7 (GND), U7.9 (GND), U20.1 (GND), U20.2 (GND), U20.5 (GND), U20.6 (GND)
unnamed: A1.11 (GPIO8), U4.3 (IN1)
unnamed: A1.12 (GPIO9), U4.2 (IN2)
unnamed: A1.14 (GPIO10), U1.3 (IN1)
unnamed: A1.15 (GPIO11), U1.2 (IN2)
unnamed: A1.16 (GPIO12), U2.3 (IN1)
unnamed: A1.17 (GPIO13), U2.2 (IN2)
unnamed: A1.19 (GPIO14), U3.3 (IN1)
unnamed: A1.20 (GPIO15), U3.2 (IN2)
unnamed: A1.21 (GPIO16), U7.3 (IN1)
unnamed: A1.22 (GPIO17), U7.2 (IN2)
unnamed: A1.29 (GPIO22), U6.3 (IN1)
unnamed: A1.31 (GPIO26_ADC0), U6.2 (IN2)
unnamed: A1.32 (GPIO27_ADC1), U5.3 (IN1)
unnamed: A1.34 (GPIO28_ADC2), U5.2 (IN2)
unnamed: J1.1, U20.3 (IN), U20.4 (IN)
unnamed: C1.2, R1.1, U1.4 (ILIM)

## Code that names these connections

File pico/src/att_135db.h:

#pragma once

#include "Attenuator.h"

/* ============================================================
 * R&S 135 dB Attenuator
 * Pads: 5 dB, 10 dB, 2×20 dB, 2×40 dB  →  max 135 dB in 5 dB steps
 * Bistabile Relais mit Set/Reset Logik: je 2 Pins pro Relais (ON / OFF)
 * ============================================================ */


/* --- U1 Relais 1: 40 dB (A) --- */
#define GPIO_135DB_40DB_ON_A     3      // GPIO3 Pin5
#define GPIO_135DB_40DB_OFF_A    2      // GPIO2 Pin4

/* --- U2 Relais 2: 20 dB (A) --- */
#define GPIO_135DB_20DB_ON_A     7      // GPIO7 Pin10
#define GPIO_135DB_20DB_OFF_A    6      // GPIO6 Pin9

/* --- U3 Relais 3:  5 dB --- */
#define GPIO_135DB_5DB_ON        9      // GPIO9 Pin12
#define GPIO_135DB_5DB_OFF       8      // GPIO8 Pin11

/* --- U4 Relais 4: 20 dB (dB) --- */
#define GPIO_135DB_20DB_ON_B    11     // GPIO11 Pin15
#define GPIO_135DB_20DB_OFF_B   10     // GPIO10 Pin14

/* --- U5 Relais 5:10 dB --- */
#define GPIO_135DB_10DB_ON      13      // GPIO13 Pin17
#define GPIO_135DB_10DB_OFF     12      // GPIO12 Pin16

/* --- U6 Relais 6:  40 dB (B) --- */
#define GPIO_135DB_40DB_ON_B    15      // GPIO15 Pin20
#define GPIO_135DB_40DB_OFF_B   14      // GPIO14 Pin19 

/* --- U7 Relais 7: RF ON/OFF --- */
#define GPIO_135DB_RF_ON        17      // GPIO17 Pin22
#define GPIO_135DB_RF_OFF       16      // GPIO16 Pin21

// /* --- U8 Relais 8: NC --- */
// #define GPIO_18                 18   // GPIO18 Pin24
// #define GPIO_22                 22   // GPIO19 Pin29

// /* --- UC Relais 9: NC --- */
// #define GPIO_27                 27   // GPIO27 Pin32
// #define GPIO_28                 28   // GPIO28 Pin34




class Att135dB : public Attenuator {
public:
    void    setup()               override;
    void    apply(int32_t dv)     override;
    int32_t     max_db()      const override { return 135; }
    int32_t     step_db()     const override { return   5; }
    int         relay_count() const override { return RELAY_COUNT; }
    const char* att_name()    const override { return "RS-135dB"; }
    int     relay_mode()  const override { return BRIDGE; }
    bool    rf_switch()   const override { return true; }
    bool    get_rf()      const override { return _states[6]; }
    void    set_rf(bool on) override;

    /* Safety watchdog: forces any relay pin LOW if it has been HIGH
     * for more than PIN_MAX_HIGH_MS milliseconds. Call from loop(). */
    void    poll()                override;

private:
    static const int              RELAY_COUNT      = 7;
    static const unsigned long    PIN_MAX_HIGH_MS  = 100;

    struct RelayDef {
        const char* name;
        int         on_pin;
        int         off_pin;
    };
    static const RelayDef _relays[7];

    bool _states[7] = {};

    /* Watchdog: timestamp (millis) when each pin was first seen HIGH.
     * Indexed [relay][0=off_pin, 1=on_pin]. 0 means "not currently HIGH". */
    unsigned long _pin_armed_ms[7][2] = {};

    static void pulse_pin(int pin);
    void        pulse(int idx, bool activate);
};

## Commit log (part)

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2026-03-15 Initial commit: LVGL8 Widget Demo for ESP32 CYD
2026-03-15 26,5 GHz Attenuator V0.5
2026-03-15 doku
2026-03-15 Board Doku
2026-03-16 cpu test
2026-03-16 webserver
2026-03-16 webserver ok
2026-03-16 ap client 1
2026-03-16 AP, Client und wlan aus implementiert
2026-03-16 default auf web und display setzten
2026-03-16 hardbeat eingebaut
2026-03-16 editfeld beim logCloick auf eine der drei Ziffern
2026-03-16 flacker der 3 Ziffern im Webentfernt
2026-03-16 Rahmen bei wlan weg
2026-03-17 GPIOs für Attenuator
2026-03-17 3 Ziffern
2026-03-17 runden auf zehner; Ausgänge low aktiv
2026-03-17 110 dB 10 dB Steps Begrenzung auch im Web
2026-03-20 Auto-Enter label
2026-03-20 wifi
2026-03-21 esp32 und pico version parallel
2026-03-21 pico minimal -> blinpy
2026-03-21 serial esp <-> pico
2026-03-21 pico display vorbereitet
2026-03-21 pico vorbereitet für mehrere abschwächer
2026-03-21 att7 tw. vorbereitet
2026-03-23 display grundsätlich ok
2026-03-23 db werte über serielle werden angezeigt
2026-03-23 bbeide serielle ok
2026-03-24 26.5GHZ Ansteuerung über uln getestet attenuator select
2026-03-24 drehregler 1
2026-03-24 bidirektionales serielle
2026-03-24 bidirektionale serielle 2
2026-03-25 Testmode
2026-03-25 erzögerung eingebaut
2026-03-25 RELAY_DEBOUNCE_TIME = 200;
2026-03-29 auto-set
2026-04-06 Schaltung
2026-04-07 auoset
2026-04-07 regler delay
2026-04-07 panel mode
2026-04-07 9 presets
2026-04-07 esp logik gpio raus
2026-04-08 test_mode
2026-04-08 vorführbar mit AP
2026-04-08 webseite Auto-Set verschoben
2026-04-08 AP und SSID Text in config
2026-04-08 webserver connect Text
2026-04-08 immer ap + client mode
2026-04-09 kicad
2026-04-09 verzögertes schalten der relais bei ap only mode behoben
2026-04-11 vorbereitet für 135dB
2026-04-11 135db Schaltung
2026-04-12 gitignore
2026-04-12 select tt impl
2026-04-12 att select
2026-04-13 a vorbereitet für jom
2026-04-13 bedienung
2026-04-13 select ziffer
2026-04-13 datdsheet
2026-04-14 pcb1
2026-04-17 schaltung PCB
2026-04-19 .gitignore Schaltung
2026-04-19 R umbenannt. div bereinigungen
2026-04-19 Bridge Labels+Trenner
2026-04-19 Schaltung new 1
2026-04-19 vor 26.5 ghz buchse ändern
2026-04-19 produktion
2026-04-19 production-files
2026-04-20 final vor nvl check
2026-04-20 Stückliste
2026-04-21 vor produktion 1
2026-04-21 produktion-version
2026-05-05 Version 1.1 der Schaltung
2026-05-06 setup 135
2026-05-06 235db dämfungswerte ok
2026-05-14 att_141
2026-05-14 att141 2
2026-05-18 display check
2026-05-28 on work cleaning
2026-06-01 pico menü
2026-06-01 Menü am ESP
2026-06-01 Menutext
2026-06-02 set modes im esp ok; menüfunktionen
2026-06-02 Menü "vehalten" OK
2026-06-02 web "verhalten" menu Version 1
2026-06-05 switch persistentz
2026-06-05 RF ON/OFF web&esp
2026-06-05 Cursor funktion OK
2026-06-05 esp optik
2026-06-06 button-set info auf deb Displays
2026-06-06 set-mode "set-button" hinweise auf esp,pico und web
2026-06-06 docu aufgeräumt
2026-06-06 copilotignoe
2026-06-07 RF on/off invertiert
2026-06-07 versionsinfo anzeigen
2026-06-07 att141
2026-06-07 att 141- Relais stimmen
2026-06-07 Versionsausgabe über uart an konsole
2026-06-07 bereinigungen
2026-06-07 grafik
2026-06-07 readme
2026-06-11 test; v erkennung
